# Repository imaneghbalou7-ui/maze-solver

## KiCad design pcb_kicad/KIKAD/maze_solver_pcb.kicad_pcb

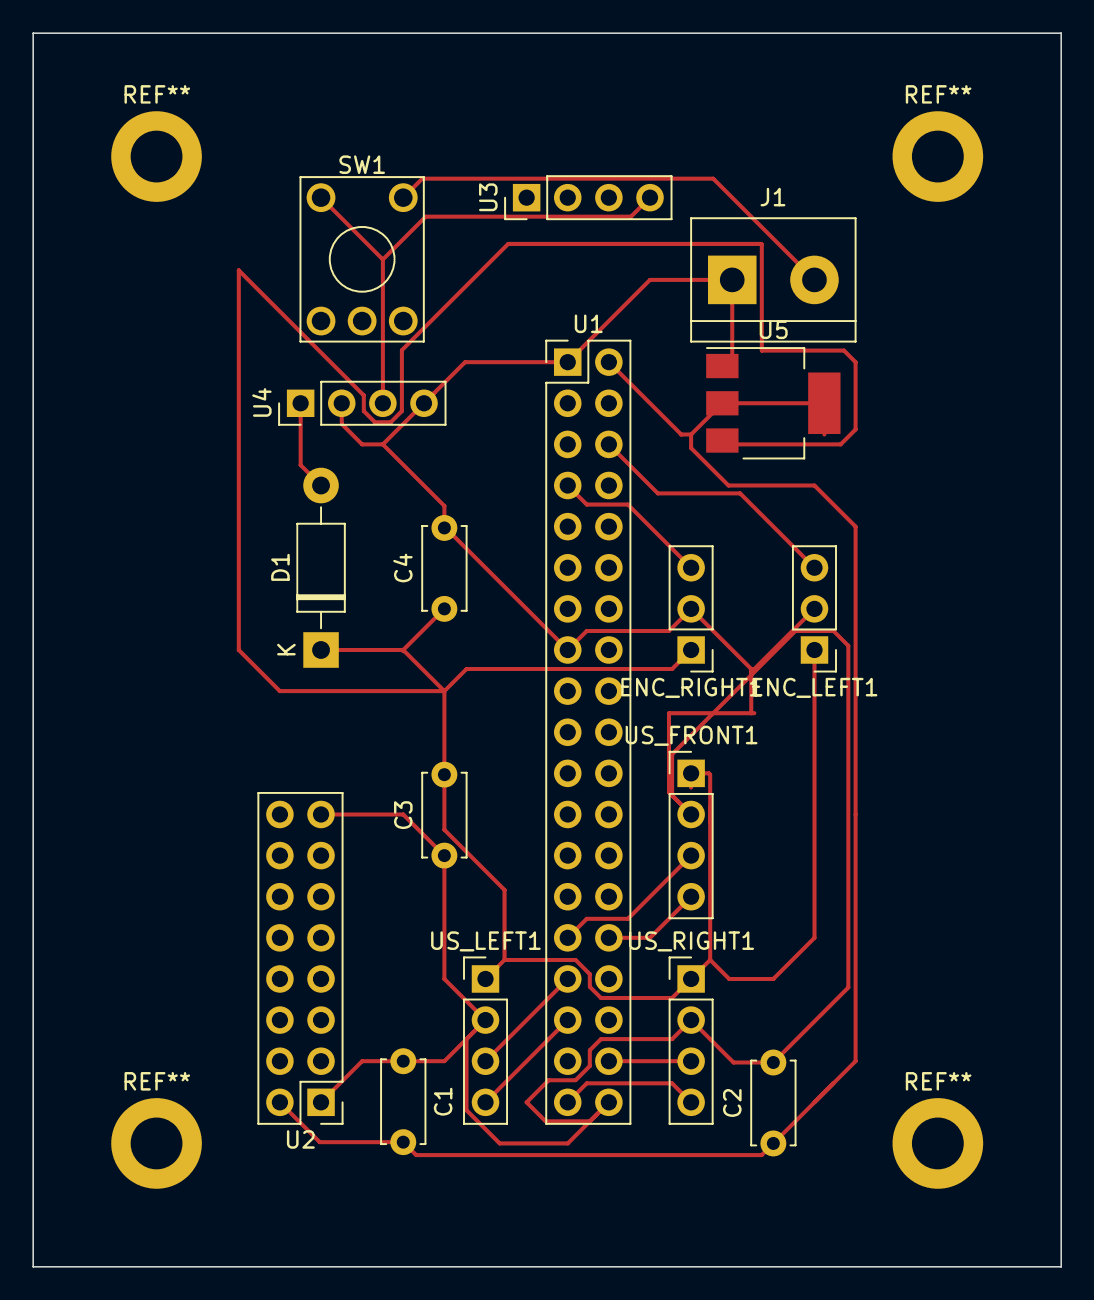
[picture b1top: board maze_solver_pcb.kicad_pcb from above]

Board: 2 copper layers, 63.5 x 76.2 mm, 17 parts (0 on the bottom side), 14 nets.

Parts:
C1, C2, C3, C4: 100nF; C_Disc_D5.0mm_W2.5mm_P5.00mm
D1: 1N4007; D_DO-41_SOD81_P10.16mm_Horizontal
ENC_LEFT1: Conn_01x03; PinHeader_1x03_P2.54mm_Vertical
ENC_RIGHT1: Conn_01x03; PinHeader_1x03_P2.54mm_Vertical
J1: Conn_01x02; TerminalBlock_bornier-2_P5.08mm
SW1: SW_SPST; KSA_Tactile_SPST
U1: ESP32-WROOM-32; PinHeader_2x19_P2.54mm_Vertical
U2: ESP32-WROOM-32; PinHeader_2x08_P2.54mm_Vertical
U3: L298; PinHeader_1x04_P2.54mm_Vertical
U4: LM2596_MODULE; PinHeader_1x04_P2.54mm_Vertical
U5: AMS1117-3.3; SOT-223-3_TabPin2
US_FRONT1: Conn_01x04; PinHeader_1x04_P2.54mm_Vertical
US_LEFT1: Conn_01x04; PinHeader_1x04_P2.54mm_Vertical
US_RIGHT1: Conn_01x04; PinHeader_1x04_P2.54mm_Vertical

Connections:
/UART_RX: U1.31 (IO19), US_LEFT1.3
/VBAT_SW: SW1.1 (A), U3.4 (Vs), U4.3 (IN+)
/VCC_3V3: C1.2, C2.1, U1.2 (VDD), U2.2 (VDD), U5.2 (VO)
GND: C1.1, C2.2, C3.1, C4.2, ENC_LEFT1.2, ENC_RIGHT1.2, J1.1, U1.1 (GND), U1.15 (GND), U1.38 (GND), U2.1 (GND), U2.15 (GND), U4.2 (OUT-), U4.4 (IN-), U5.1 (GND), US_FRONT1.2, US_LEFT1.2, US_RIGHT1.2
unnamed: C3.2, C4.1, D1.1 (K), ENC_LEFT1.1, ENC_RIGHT1.1, U5.3 (VI), US_FRONT1.1, US_LEFT1.1, US_RIGHT1.1
unnamed: D1.2 (A), U4.1 (OUT+)
unnamed: ENC_LEFT1.3, U1.6 (IO34)
unnamed: ENC_RIGHT1.3, U1.7 (IO35)
unnamed: J1.2, SW1.2 (B)
unnamed: U1.29 (IO5), US_FRONT1.3
unnamed: U1.30 (IO18), US_FRONT1.4
unnamed: U1.33 (IO21), US_LEFT1.4
unnamed: U1.36 (IO22), US_RIGHT1.3
unnamed: U1.37 (IO23), US_RIGHT1.4

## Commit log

2026-05-07 Structure initiale du projet
2026-06-07 Initialisation de la structure du projet Maze Solver
2026-06-18 PCB KiCad complet - ESP32CAM + KCD1
